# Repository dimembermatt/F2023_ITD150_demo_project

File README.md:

# F2023_ITD150_demo_project
Demo project for F2023_ITD150.

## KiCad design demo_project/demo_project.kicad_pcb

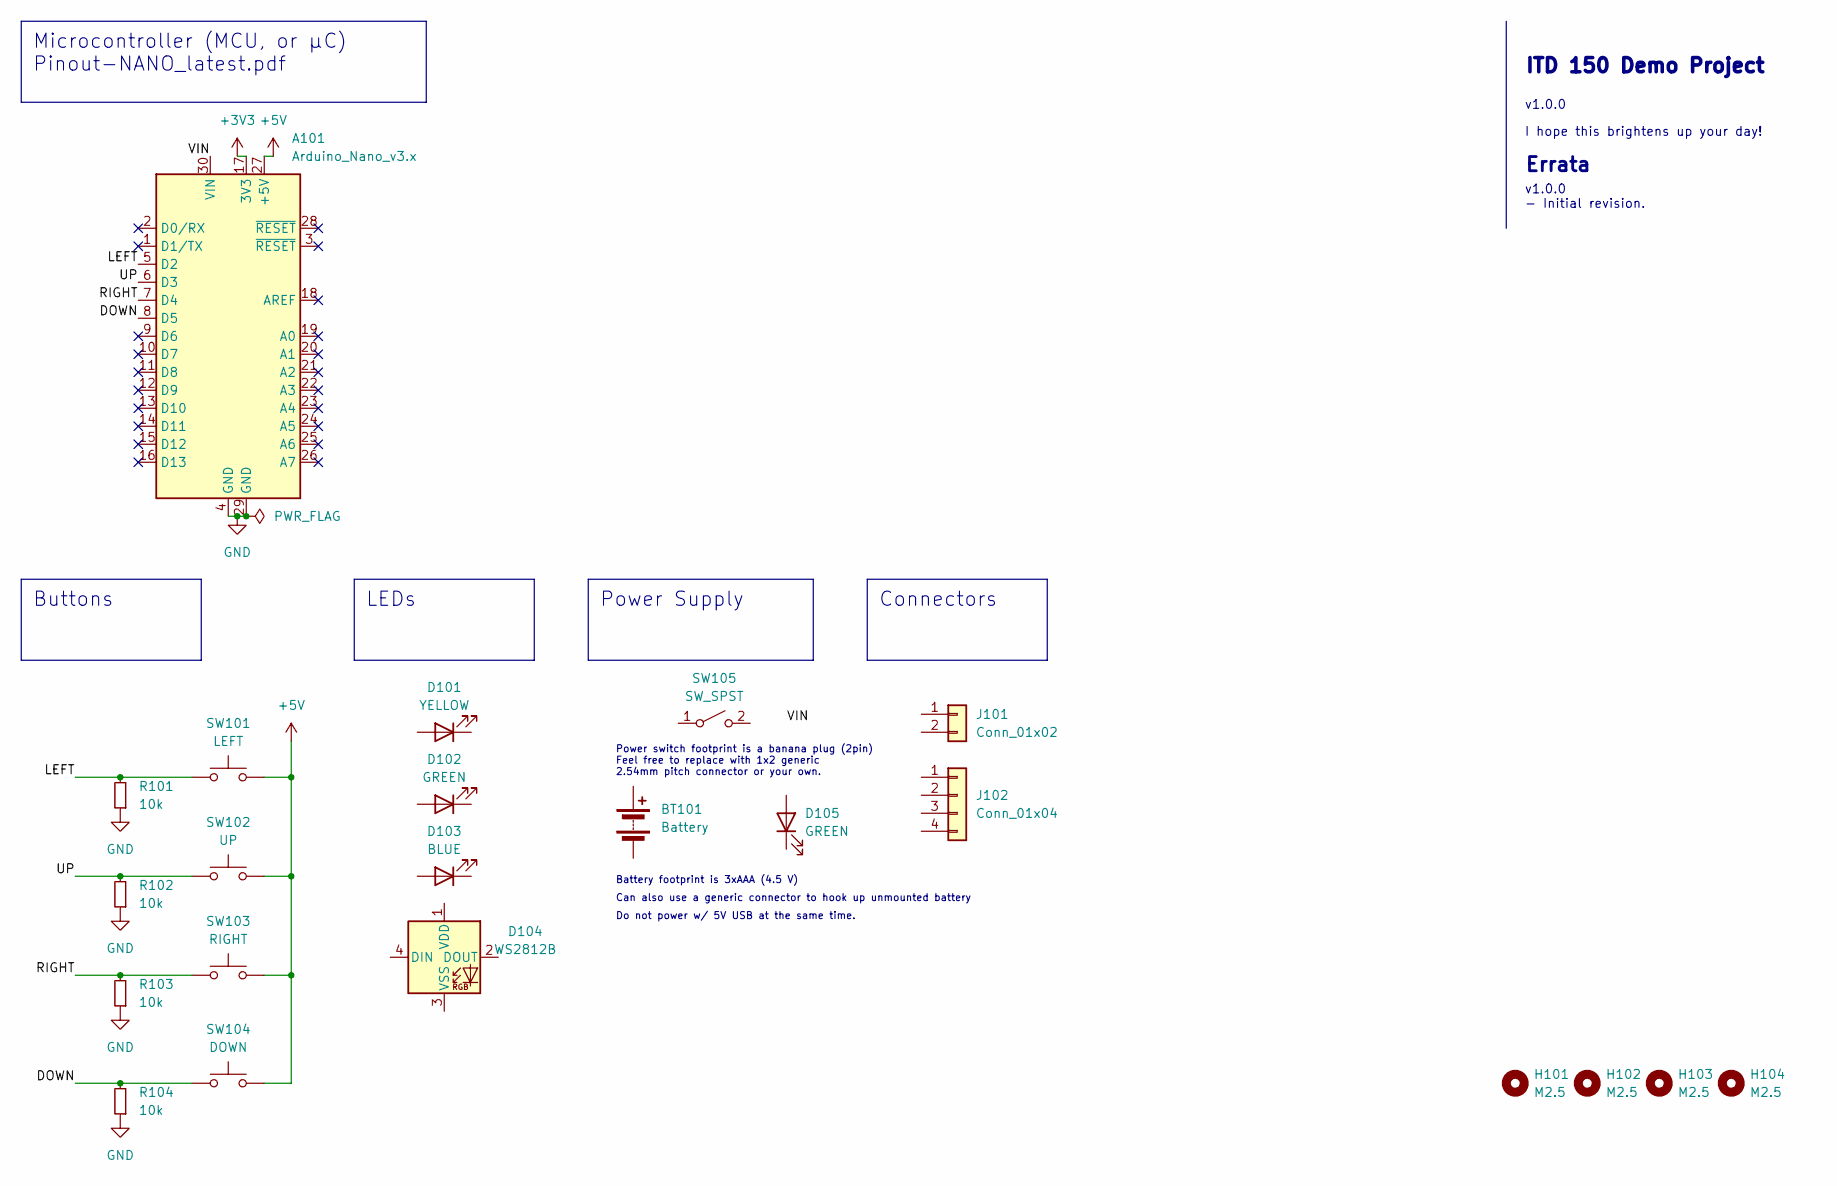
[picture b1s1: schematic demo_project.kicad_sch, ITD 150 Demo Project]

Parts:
A101: Arduino_Nano_v3.x; Arduino_Nano
BT101: Battery; BatteryHolder_Keystone_2479_3xAAA
D101: YELLOW; LED_D3.0mm_FlatTop
D102, D105: GREEN; LED_D3.0mm_FlatTop
D103: BLUE; LED_D3.0mm_FlatTop
D104: WS2812B; LED_WS2812B_PLCC4_5.0x5.0mm_P3.2mm
H101, H102, H103, H104: M2.5; MountingHole_2.7mm_M2.5
J101: Conn_01x02; PinSocket_1x02_P2.54mm_Vertical
J102: Conn_01x04; PinSocket_1x04_P2.54mm_Vertical
R101, R102, R103, R104: 10k; R_Axial_DIN0207_L6.3mm_D2.5mm_P10.16mm_Horizontal
SW101: LEFT; SW_PUSH_6mm_H4.3mm
SW102: UP; SW_PUSH_6mm_H4.3mm
SW103: RIGHT; SW_PUSH_6mm_H4.3mm
SW104: DOWN; SW_PUSH_6mm_H4.3mm
SW105: SW_SPST; Banana_Jack_2Pin

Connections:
+3V3: A101.17 (3V3)
+5V: A101.27 (+5V), SW101.2, SW102.2, SW103.2, SW104.2
/DOWN: A101.8 (D5), R104.2, SW104.1
/LEFT: A101.5 (D2), R101.2, SW101.1
/RIGHT: A101.7 (D4), R103.2, SW103.1
/UP: A101.6 (D3), R102.2, SW102.1
/VIN: A101.30 (VIN)
GND: A101.4 (GND), A101.29 (GND), R101.1, R102.1, R103.1, R104.1

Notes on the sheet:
Connectors
Microcontroller (MCU, or μC) Pinout-NANO_latest.pdf
LEDs
Buttons
Power Supply
Power switch footprint is a banana plug (2pin) Feel free to replace with 1x2 generic 2.54mm pitch connector or your own.
Battery footprint is 3xAAA (4.5 V)
v1.0.0
I hope this brightens up your day!
Can also use a generic connector to hook up unmounted battery
Errata
ITD 150 Demo Project
Do not power w/ 5V USB at the same time.
v1.0.0 - Initial revision.

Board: 2 copper layers, 22 parts (0 on the bottom side), 6 nets, no tracks yet.

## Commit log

2023-09-07 v1.0.0 prod version
2023-10-04 blank sch starter
